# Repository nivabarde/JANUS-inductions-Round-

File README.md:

# JANUS-inductions-Round-

# Team JANUS CanSat 2025-2026 – Avionics Subsystem Solutions

This repository contains the solutions for the final round problems of the Team JANUS CanSat 2025-2026 competition. The solutions cover:

1. Flight Software – Arduino code for GPS parsing and flight state machine.
2. Ground Control System – Web interface for live plotting of sensor and GPS data using Chart.js.
3. PCB Design – KiCad PCB layout for STM32-based board with BMP290 sensor.

Solution 1: Flight Software

Objective:
Set up the Quectel L89HA GNSS Module to receive GPS data, print it, and implement a flight state machine.

Features Implemented:

* Reads and parses NMEA sentences (GNRMC & GNGGA).
* Prints time, latitude, longitude, and altitude to the Serial Monitor.
* Implements flight state machine with six states:
* Assumes a normal flight path (ascend → apogee → descend).

Usage:

1. Connect the Quectel L89HA GNSS module to the Arduino.
2. Upload the  FlightSoftware.ino sketch.
3. Open Serial Monitor to see live GPS data and state transitions.

Solution 2: Ground Control System

Objective:
Create a web-based interface to read Arduino sensor data via Web Serial API and plot it live.

Features Implemented:

* Live 2D plotting of sensor values using Chart.js.
* 3D-like visualization of **latitude, longitude, and altitude** with color-coded altitude.
* Supports both **simulated data** and live Arduino data.

 Solution 3: PCB Design

Objective:
Design a PCB in KiCad for an STM32-based board with BMP290 sensor and USB-B power port.

Features Implemented:

* Correct component placement and routing according to schematic.
* Separate trace widths for **power** and **signal lines**.
* **Ground plane** on bottom layer with appropriate vias.
* Fully manual routing (no auto-router used).

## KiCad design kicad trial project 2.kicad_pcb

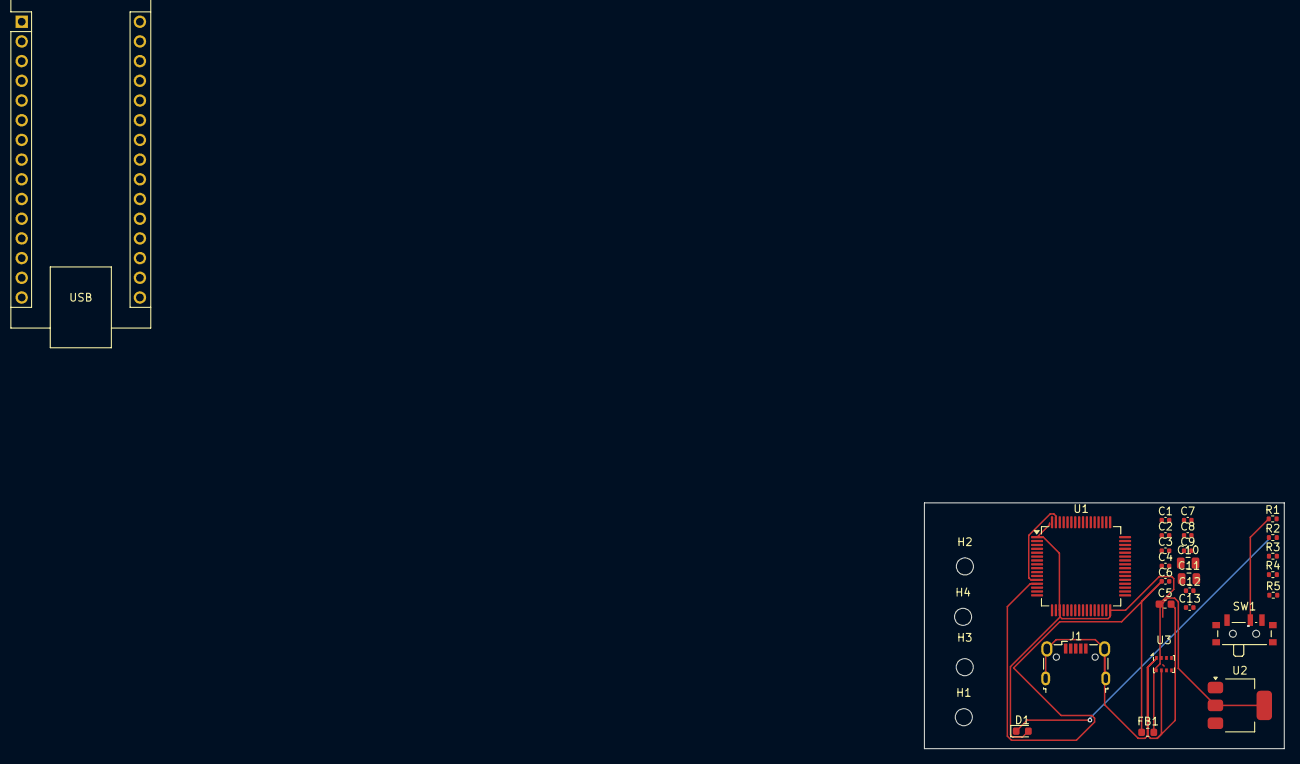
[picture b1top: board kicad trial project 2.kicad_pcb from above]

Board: 2 copper layers, 46.4 x 31.7 mm, 30 parts (0 on the bottom side), 14 nets.

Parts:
A1: Arduino_Nano_v3.x; Arduino_Nano
C1, C2, C3, C4, C9, C12, C13: 100n; C_0402_1005Metric
C5: 10u; C_0603_1608Metric
C6: 10n; C_0402_1005Metric
C7, C8: 1u; C_0402_1005Metric
C10, C11: 22u; C_0805_2012Metric
D1: RED; LED_0603_1608Metric
FB1: 120R; L_0603_1608Metric
H1, H2, H3, H4: MountingHole; MountingHole_2.2mm_M2
J1: USB_B_Micro; USB_Micro-B_Wuerth_629105150521
R1, R3, R4, R5: 10k; R_0402_1005Metric
R2: 1k; R_0402_1005Metric
SW1: SW_SPDT; SW_SPDT_PCM12
U1: STM32L476RGTx; LQFP-64_10x10mm_P0.5mm
U2: AMS1117-3.3; SOT-223-3_TabPin2
U3: BMP280; Bosch_LGA-8_2x2.5mm_P0.65mm_ClockwisePinNumbering

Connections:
+3.3V: C1.1, C2.1, C3.1, C4.1, C5.1, C8.1, C11.1, C12.2, C13.2, D1.2 (A), FB1.2, R4.2, R5.2, SW1.3 (C), U1.1 (VBAT), U1.19 (VDD), U1.32 (VDD), U1.64 (VDD), U2.2 (VO), U3.2 (CSB), U3.6 (VDDIO), U3.8 (VDD)
+3.3VA: C6.1, C7.1, FB1.1, U1.13 (VDDA)
+5V: A1.5 (D2), A1.6 (D3), A1.7 (D4), A1.27 (+5V)
/BOOT0: R1.2, U1.60 (BOOT0)
/I2C1_SCL: R4.1, U1.58 (PB6), U3.4 (SCK)
/I2C1_SDA: R5.1, U1.59 (PB7), U3.3 (SDI)
/NRST: C9.1, U1.7 (NRST)
/SW_BOOT0: R1.1, SW1.2 (B)
/USB_OTG_FS_DM-: J1.2 (D-), U1.44 (PA11)
/USB_OTG_FS_DP+: J1.3 (D+), U1.45 (PA12)
GND: A1.4 (GND), A1.29 (GND), C1.2, C2.2, C3.2, C4.2, C5.2, C6.2, C7.2, C8.2, C9.2, C10.2, C11.2, C12.1, C13.1, J1.5 (GND), J1.6 (Shield), R2.2, R3.1, SW1.1 (A), U1.12 (VSSA), U1.18 (VSS), U1.31 (VSS), U1.47 (VSS), U1.63 (VSS), U2.1 (GND), U3.1 (GND), U3.7 (GND)
unnamed: D1.1 (K), R2.1
unnamed: R3.2, U3.5 (SDO)
VBUS: C10.1, J1.1 (VBUS), U2.3 (VI)
